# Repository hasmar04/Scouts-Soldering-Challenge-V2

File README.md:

# Scouts-Soldering-Challenge-V2

A soldering challenge suitable for Scouts all the way to Rovers, without using an Arduino. 

As a member of the Australian Scouting movement, the logo has been used within this design for the purpose of promoting the movement, and to help the project to the target audience of Scouting members. 

For more information and/or assistance with implementing this challenge in your own Scout group, contact me at [246328@scoutsqld.com.au](mailto:246328@scoutsqld.com.au) 

### For more information on the Australian Scouting Movement, visit https://scouts.com.au/

## Components Required
- 1x PCB (see 'pcb' folder)
- 2x Red LED
- 1x Green LED
- 1x Yellow LED
- 1x Orange LED
- 5x 51 ohm resistor
- 1x 6x6mm push button
- 1x Buzzer
- 1x Battery Holder

More information can be found in the [Procurement Guide](/docs/Procurement%20Guide.md)

## Documentation
Documentation can be found in the [/docs](/docs) folder. This includes:
- Procurement Guide
- Assembly Guide

## Contributing
If there is anything that you think is missing from this repository, or you find an error, please [create an issue](</issues>) or fix it yourself and create a pull request.

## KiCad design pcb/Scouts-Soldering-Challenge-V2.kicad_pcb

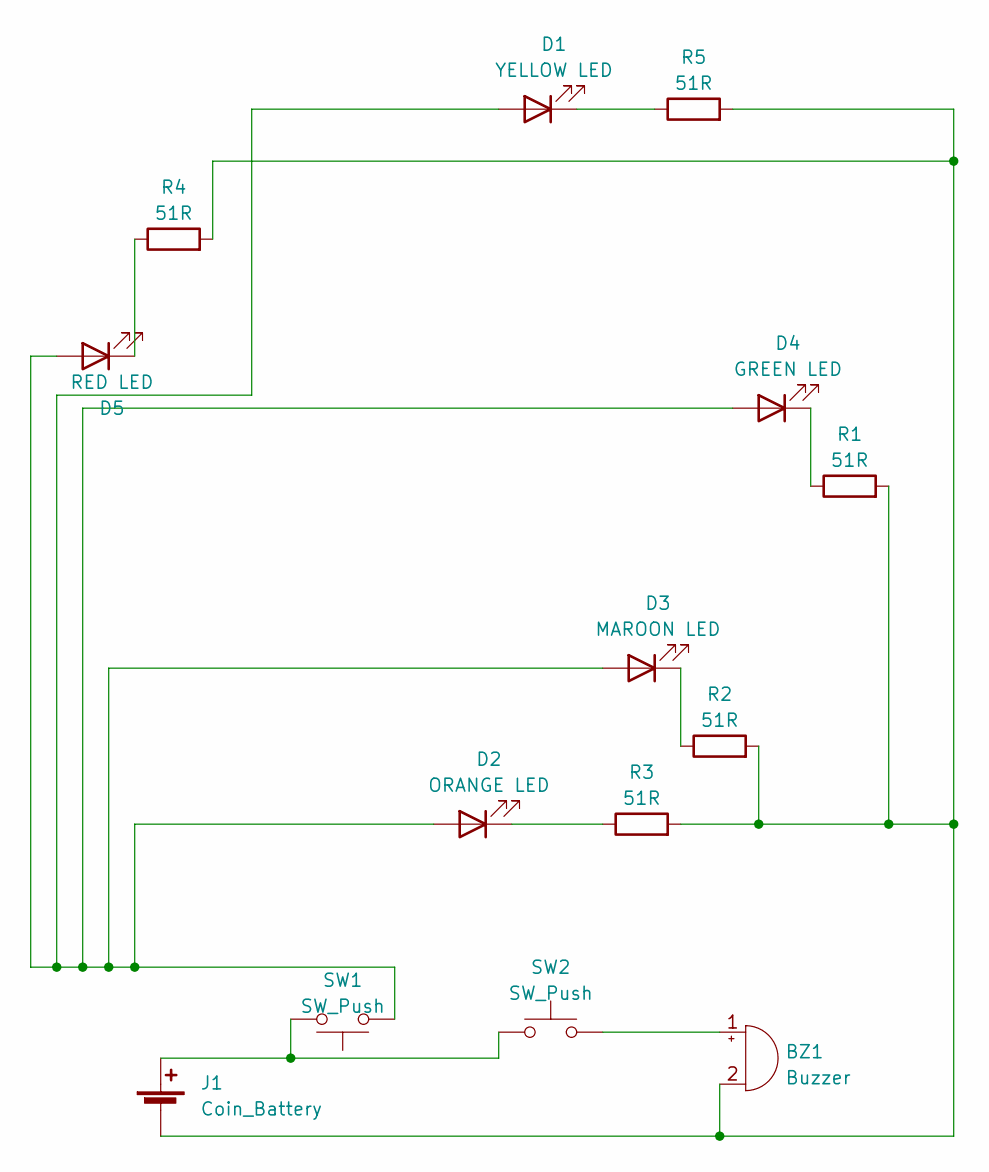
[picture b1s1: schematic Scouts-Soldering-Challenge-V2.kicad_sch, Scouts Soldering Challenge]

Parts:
BZ1: Buzzer; Buzzer_TDK_PS1240P02BT_D12.2mm_H6.5mm
D1: YELLOW LED; LED_D3.0mm
D2: ORANGE LED; LED_D3.0mm
D3: MAROON LED; LED_D3.0mm
D4: GREEN LED; LED_D3.0mm
D5: RED LED; LED_D3.0mm
J1: Coin_Battery; BatteryHolder_Keystone_103_1x20mm
R1, R2, R3, R4, R5: 51R; R_Axial_DIN0207_L6.3mm_D2.5mm_P10.16mm_Horizontal
SW1, SW2: SW_Push; SW_PUSH_6mm

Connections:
unnamed: BZ1.2 (+), J1.2 (-), R1.2, R2.2, R3.2, R4.2, R5.2
unnamed: BZ1.1 (-), SW2.2
unnamed: D1.2 (A), D2.2 (A), D3.2 (A), D4.2 (A), D5.2 (A), SW1.1
unnamed: D1.1 (K), R5.1
unnamed: D2.1 (K), R3.1
unnamed: D3.1 (K), R2.1
unnamed: D4.1 (K), R1.1
unnamed: D5.1 (K), R4.1
unnamed: J1.1 (+), SW1.2, SW2.1

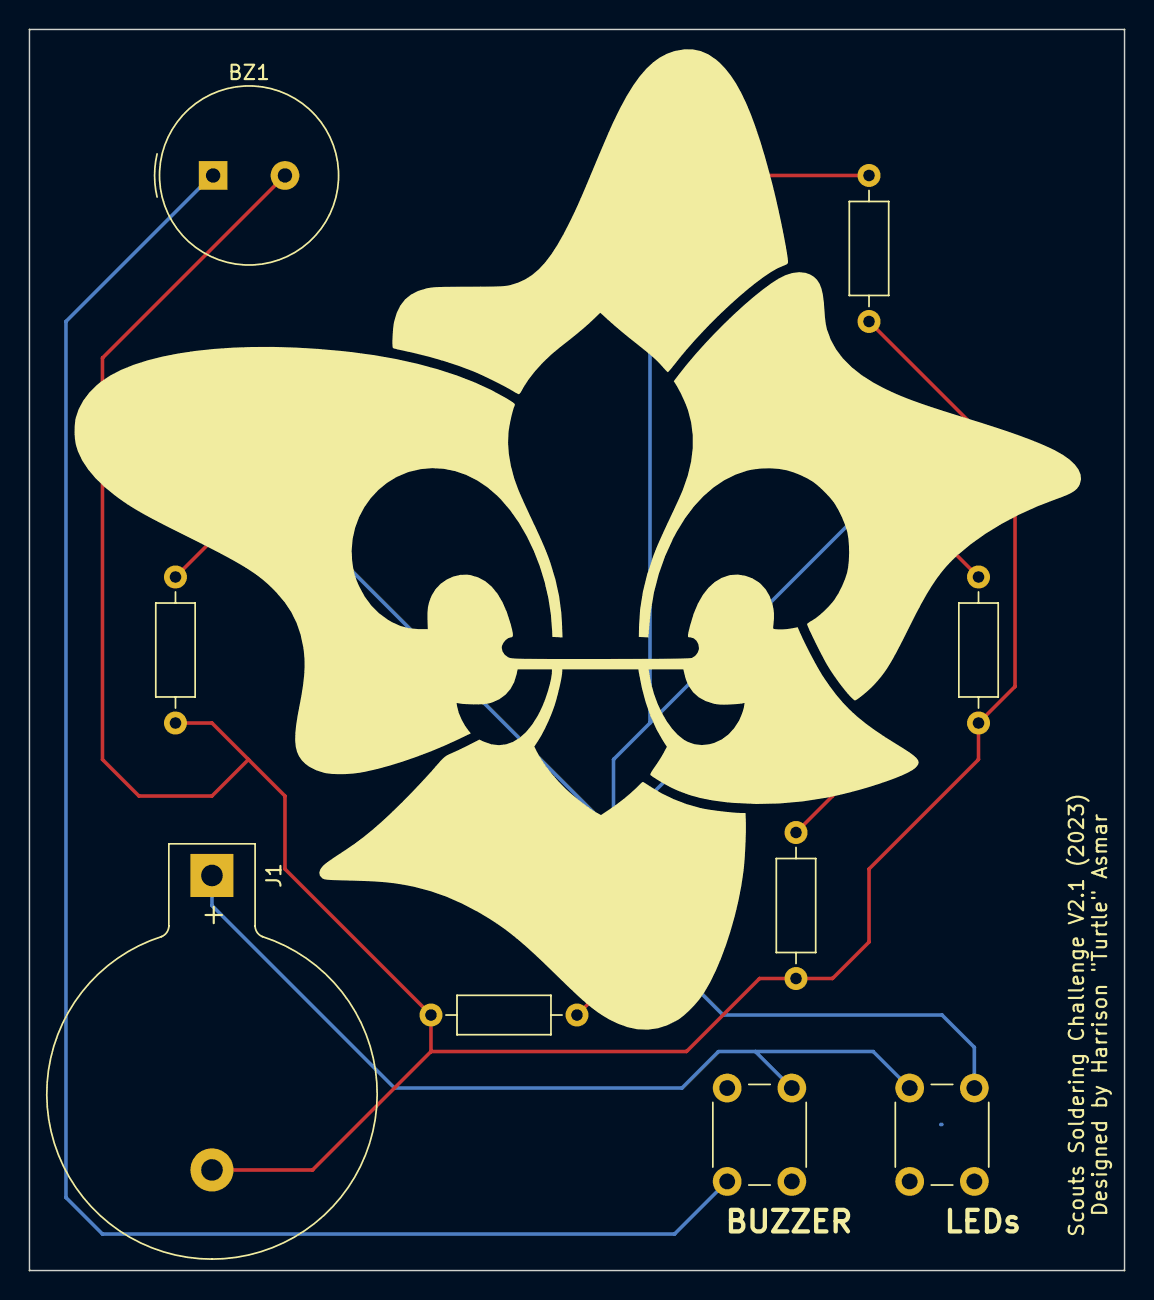
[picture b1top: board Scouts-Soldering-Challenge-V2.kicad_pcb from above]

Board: 2 copper layers, 76.2 x 86.4 mm, 14 parts (0 on the bottom side), 9 nets.

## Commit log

2023-08-26 Initial Repo Upload
    Includes new PCB design with aligned documentation. Also stripped all files that are not needed with the lack of Arduino.
2023-09-05 Removed lingering references to Arduino
    Made sure all references to Arduino are removed from the Assembly Guide
2023-09-05 Silkscreen version update to V2.0
2023-09-05 Added renders of the board
2023-09-22 Add lck files to gitignore
2023-09-22 Update documentation and readme
2023-09-22 Add new renders
2023-09-22 V2.1 of PCB and Schematic
    Complete overhall, adds a buzzer, replaces the barrel jack with a battery and changes the resistors to match. Also moves things around a lot.
2023-09-22 Update README.md
    I am clearly blind
2023-10-14 Updated buzzer info in procurement guide
    Bought the wrong buzzers, these ones should work
